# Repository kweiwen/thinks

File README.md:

# thinks
* a modification eurorack project based on mutable links
* same value as the original links but with through hole compoments

# tested and finished

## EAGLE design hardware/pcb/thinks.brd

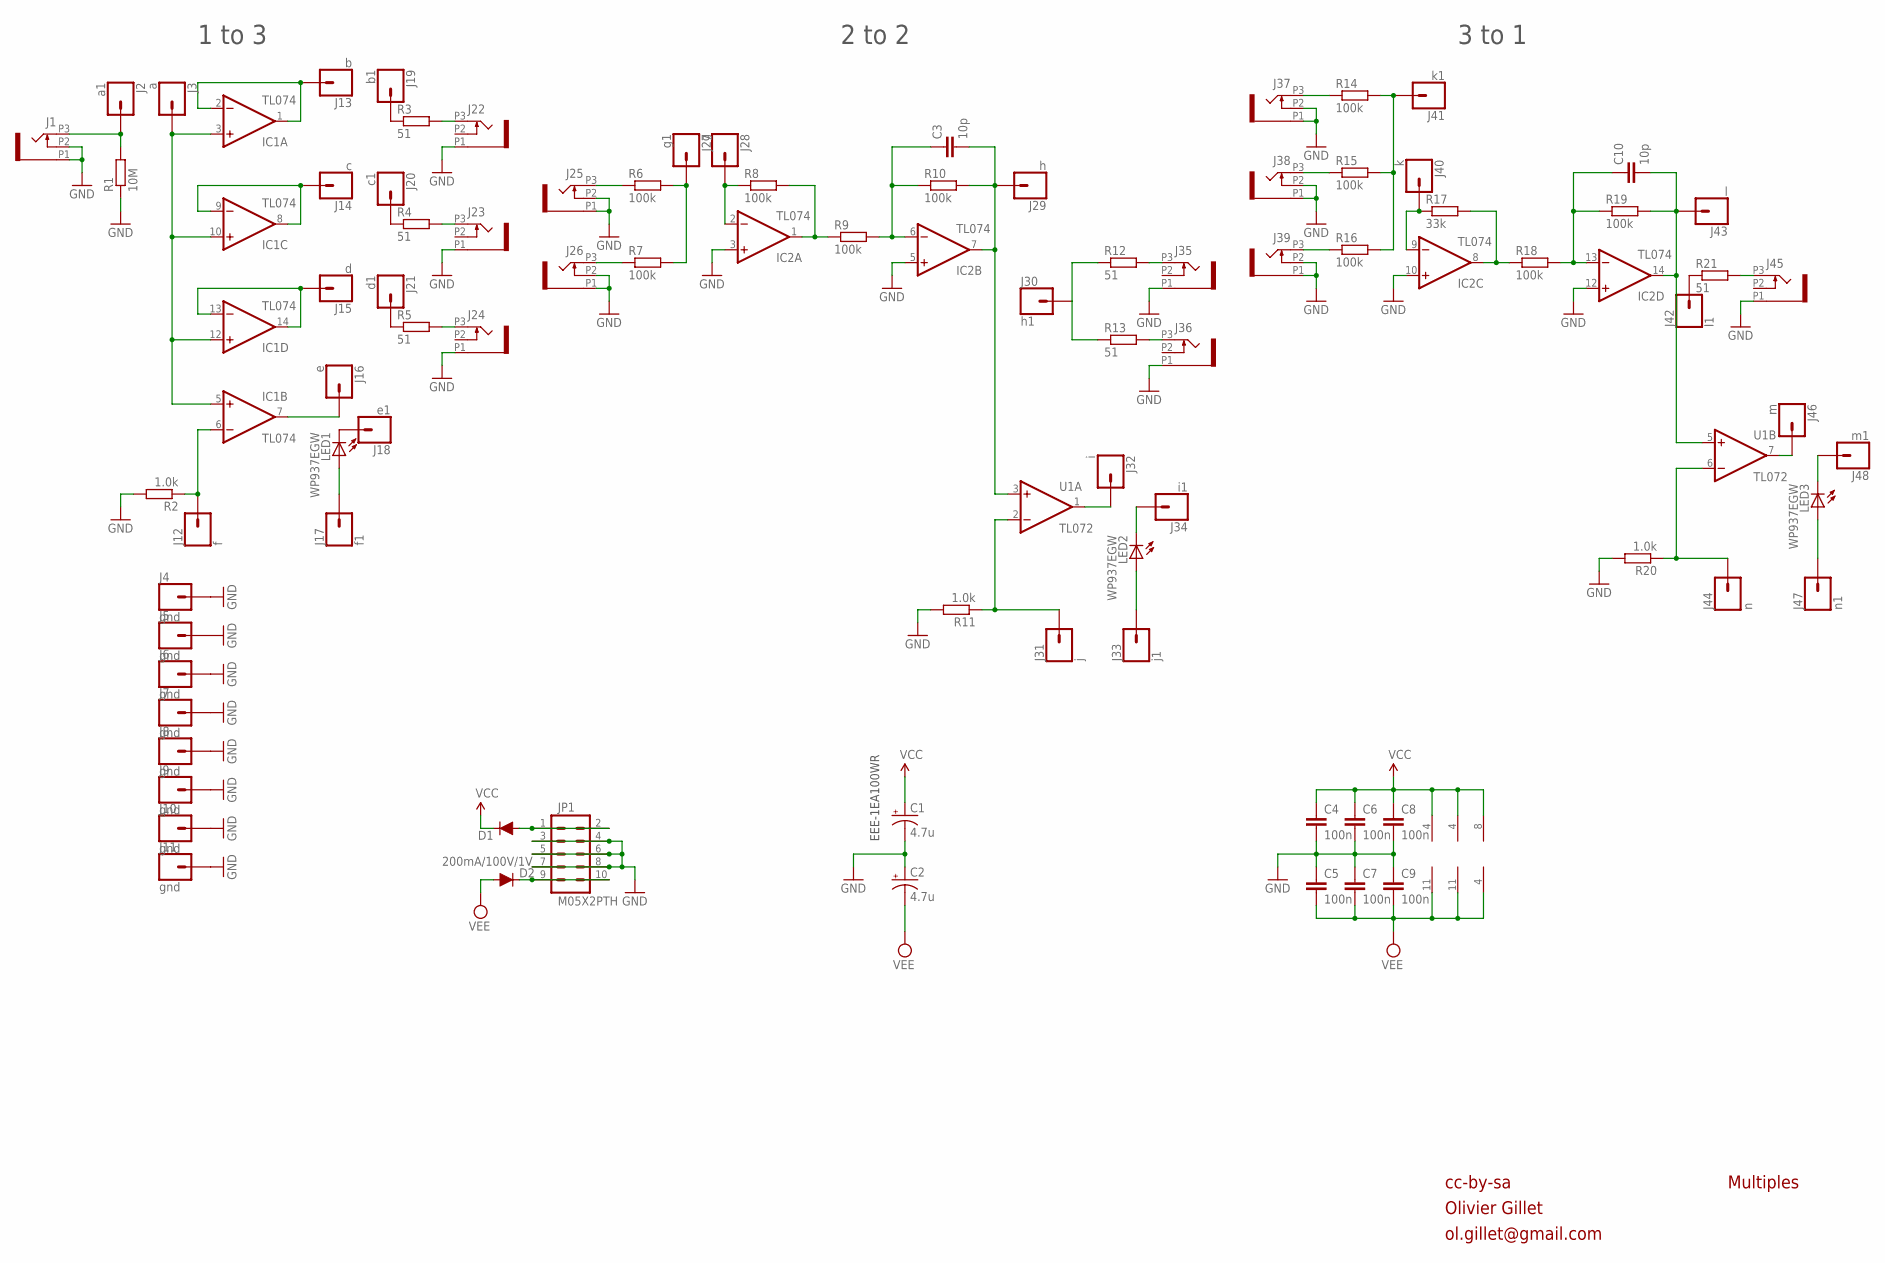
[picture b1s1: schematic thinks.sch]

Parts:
C1, C2: 4.7u; E2,5-6
C3, C10: 10p; C5B2.5
C4, C5, C6, C7, C8, C9: 100n; C5B2.5
D1, D2: 200mA/100V/1V; DIODE-1N4148
IC1, IC2: TL074; DIL14
J1, J22, J23, J24, J25, J26, J35, J36, J37, J38, J39, J45: PJ301_THONKICONN6; WQP_PJ_301M6
J2: a1; 1X01
J3: a; 1X01
J4, J5, J6, J7, J8, J9, J10, J11: gnd; 1X01
J12: f; 1X01
J13: b; 1X01
J14: c; 1X01
J15: d; 1X01
J16: e; 1X01
J17: f1; 1X01
J18: e1; 1X01
J19: b1; 1X01
J20: c1; 1X01
J21: d1; 1X01
J27: g1; 1X01
J28: g; 1X01
J29: h; 1X01
J30: h1; 1X01
J31: j; 1X01
J32: i; 1X01
J33: j1; 1X01
J34: i1; 1X01
J40: k; 1X01
J41: k1; 1X01
J42: l1; 1X01
J43: l; 1X01
J44: n; 1X01
J46: m; 1X01
J47: n1; 1X01
J48: m1; 1X01
JP1: M05X2PTH; AVR_ICSP
LED1, LED2, LED3: WP937EGW; LED3MM
R1: 10M; VERTICAL_RESISTOR
R2, R11, R20: 1.0k; VERTICAL_RESISTOR
R3, R4, R5, R12, R13, R21: 51; VERTICAL_RESISTOR
R6, R7, R8, R9, R10, R14, R15, R16, R18, R19: 100k; VERTICAL_RESISTOR
R17: 33k; VERTICAL_RESISTOR
U1: TL072; DIL08

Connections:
GND: C1.-, C2.+, C4.2, C5.1, C6.2, C7.1, C8.2, C9.1, IC2.3 (+IN), IC2.5 (+IN), IC2.10 (+IN), IC2.12 (+IN), J1.P1 (1), J1.P2 (2), J4.1, J5.1, J6.1, J7.1, J8.1, J9.1, J10.1, J11.1, J22.P1 (1), J23.P1 (1), J24.P1 (1), J25.P1 (1), J25.P2 (2), J26.P1 (1), J26.P2 (2), J35.P1 (1), J36.P1 (1), J37.P1 (1), J37.P2 (2), J38.P1 (1), J38.P2 (2), J39.P1 (1), J39.P2 (2), J45.P1 (1), JP1.3, JP1.4, JP1.5, JP1.6, JP1.7, JP1.8, R1.1, R2.2, R11.2, R20.2
unnamed: IC2.1 (OUT), R8.2, R9.1
unnamed: J39.P3 (3), R16.1
unnamed: IC1.1 (OUT), IC1.2 (-IN), J13.1
unnamed: IC1.8 (OUT), IC1.9 (-IN), J14.1
unnamed: IC1.13 (-IN), IC1.14 (OUT), J15.1
unnamed: D1.A, JP1.1, JP1.2
unnamed: IC1.3 (+IN), IC1.5 (+IN), IC1.10 (+IN), IC1.12 (+IN), J3.1
unnamed: IC1.7 (OUT), J16.1
unnamed: J38.P3 (3), R15.1
unnamed: J26.P3 (3), R7.1
unnamed: J22.P3 (3), R3.2
unnamed: J23.P3 (3), R4.2
unnamed: J24.P3 (3), R5.2
unnamed: J34.1, LED2.K (C)
unnamed: J25.P3 (3), R6.1
unnamed: J36.P3 (3), R13.2
unnamed: J35.P3 (3), R12.2
unnamed: C10.2, IC2.14 (OUT), J43.1, R19.2, U1.5 (+IN)
unnamed: J44.1, R20.1, U1.6 (-IN)
unnamed: D2.C, JP1.9, JP1.10
unnamed: IC1.6 (-IN), J12.1, R2.1
unnamed: J37.P3 (3), R14.1
unnamed: J45.P3 (3), R21.2
unnamed: J41.1, R14.2, R15.2, R16.2
unnamed: IC2.8 (OUT), R17.2, R18.1
unnamed: C3.2, IC2.7 (OUT), J29.1, R10.2, U1.3 (+IN)
unnamed: C10.1, IC2.13 (-IN), R18.2, R19.1
unnamed: J1.P3 (3), J2.1, R1.2
unnamed: J31.1, R11.1, U1.2 (-IN)
unnamed: J48.1, LED3.K (C)
unnamed: J27.1, R6.2, R7.2
unnamed: C3.1, IC2.6 (-IN), R9.2, R10.1
unnamed: J19.1, R3.1
unnamed: J20.1, R4.1
unnamed: J21.1, R5.1
unnamed: J17.1, LED1.A
unnamed: J18.1, LED1.K (C)
unnamed: IC2.2 (-IN), J28.1, R8.1
unnamed: J30.1, R12.1, R13.1
unnamed: IC2.9 (-IN), J40.1, R17.1
unnamed: J33.1, LED2.A
unnamed: J32.1, U1.1 (OUT)
unnamed: J42.1, R21.1
unnamed: J46.1, U1.7 (OUT)
unnamed: J47.1, LED3.A
VCC: C1.+, C4.1, C6.1, C8.1, D1.C, IC1.4 (V+), IC2.4 (V+), U1.8 (V+)
VEE: C2.-, C5.2, C7.2, C9.2, D2.A, IC1.11 (V-), IC2.11 (V-), U1.4 (V-)

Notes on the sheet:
cc-by-sa
Olivier Gillet
ol.gillet@gmail.com
Multiples
1 to 3
2 to 2
3 to 1
EEE-1EA100WR

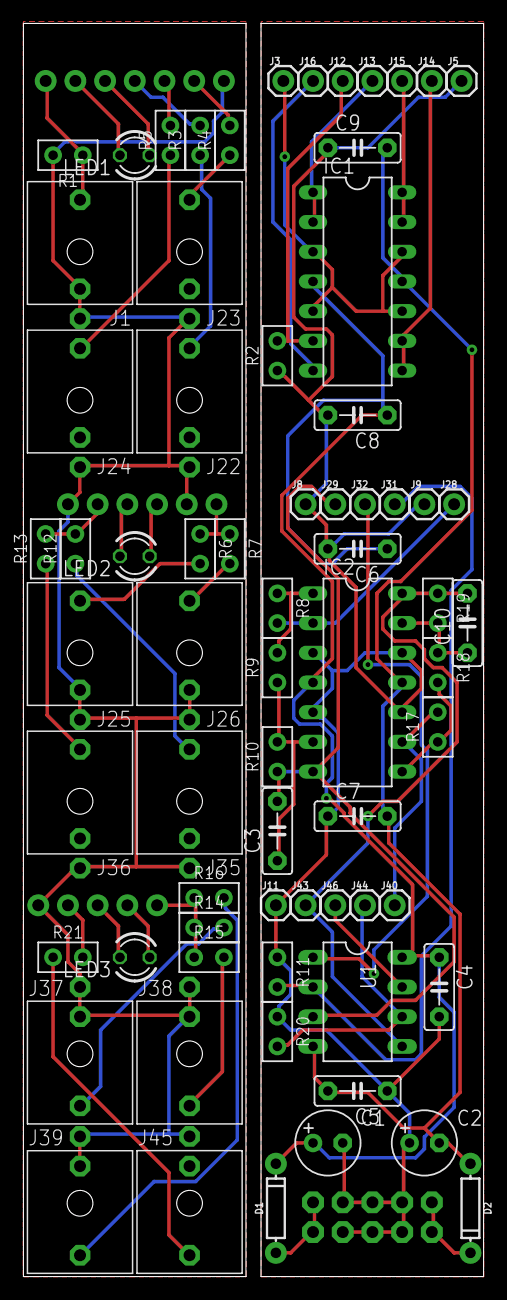
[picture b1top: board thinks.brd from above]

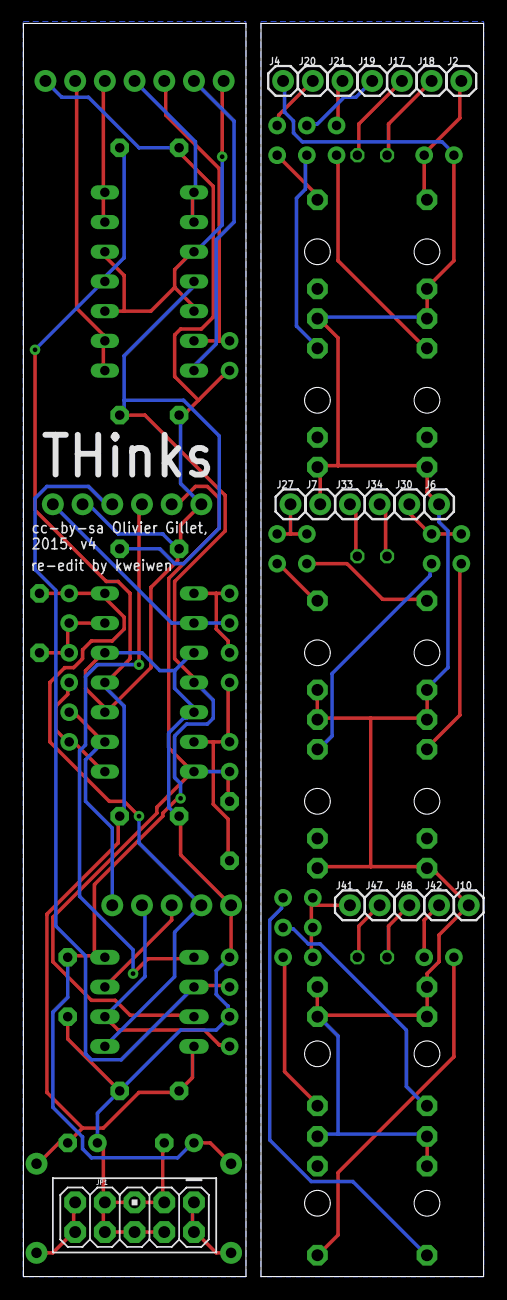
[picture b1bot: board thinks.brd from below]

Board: 2 copper layers, 39.4 x 107.2 mm, 88 parts (19 on the bottom side), 48 nets.

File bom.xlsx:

Table 1
Qty | Value | Device | Package | Parts | Description
6 | 100n | C5/2.5 | C5B2.5 | C4, C5, C6, C7, C8, C9 | CAPACITOR
2 | 10p | C5/2.5 | C5B2.5 | C3, C10 | CAPACITOR
18 | MALE_PINHD | CONN_01 | 1X01 |  | Single connection point. Often used as Generic Header-pin footprint for 0.1 inc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
18 | FEMALE_PINHD | CONN_01 | 1X01 |  | Single connection point. Often used as Generic Header-pin footprint for 0.1 inc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
2 | 4.7u | CPOL-USE2.5-6 | E2,5-6 | C1, C2 | POLARIZED CAPACITOR, American symbol
2 | 200mA/100V/1V | DIODE-1N4148 | DIODE-1N4148 | D1, D2 | Diode
3 | WP937EGW | LED | 3MM | LED1, LED2, LED3 | LED
1 | M05X2PTH | M05X2PTH |  | JP1 | Header 5x2
12 | PJ301_THONKICONN6 | PJ301_THONKICONN6 | WQP_PJ_301M6 | J1, J22, J23, J24, J25, J26, J35, J36, J37, J38, J39, J45
3 | 1.0k | RESISTOR*VERTICAL | VERTICAL_RESISTOR | R2, R11, R20 | Standard resistor, various versions
10 | 100k | RESISTOR*VERTICAL | VERTICAL_RESISTOR | R6, R7, R8, R9, R10, R14, R15, R16, R18, R19 | Standard resistor, various versions
1 | 10M | RESISTOR*VERTICAL | VERTICAL_RESISTOR | R1 | Standard resistor, various versions
1 | 33k | RESISTOR*VERTICAL | VERTICAL_RESISTOR | R17 | Standard resistor, various versions
6 | 51 | RESISTOR*VERTICAL | VERTICAL_RESISTOR | R3, R4, R5, R12, R13, R21 | Standard resistor, various versions
1 | TL072 | TL072P | DIL08 | U1 | Generic Dual Op Amp
2 | TL074 | TL074P | DIL14 | IC1, IC2 | OP AMP

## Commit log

2017-09-19 Schematic

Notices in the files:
parts and their libraries:
SparkFun-DiscreteSemi: Licensing: Creative Commons ShareAlike 4.0 International - https://creativecommons.org/licenses/by-sa/4.0
